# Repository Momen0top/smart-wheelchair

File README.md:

# SmartChair v3 — Complete System

A locally controlled smart robotic wheelchair with Raspberry Pi 3B, 2D LIDAR mapping, A* autonomous navigation, and a Flutter mobile app.

## Project Structure

```
chair/
├── backend/                        # Raspberry Pi (Python/FastAPI)
│   ├── main.py                     # FastAPI + WebSocket server
│   ├── config.py                   # GPIO pins, map grid, safety
│   ├── models.py                   # Pydantic models
│   ├── utils.py                    # Logging
│   ├── motor_controller.py         # 2× L298N DC motor control
│   ├── lidar_scanner.py            # Stepper + VL53L0X 360° scanner
│   ├── mapping_engine.py           # Occupancy grid + Bresenham ray-cast
│   ├── navigator.py                # A* pathfinding + autonomous drive
│   ├── room_manager.py             # rooms.json CRUD
│   ├── command_interpreter.py      # NLP intent extraction
│   ├── pairing.py                  # QR code generation
│   ├── requirements.txt
│   └── test_interpreter.py
│
├── wheelchair_app/                 # Flutter mobile app
│   ├── pubspec.yaml
│   ├── android/.../AndroidManifest.xml
│   └── lib/
│       ├── main.dart               # App shell + bottom nav
│       ├── models/models.dart      # Data classes
│       ├── services/
│       │   ├── api_service.dart    # REST client
│       │   ├── websocket_service.dart # Live map
│       │   └── speech_service.dart # Voice
│       ├── widgets/
│       │   ├── map_painter.dart    # Occupancy grid renderer
│       │   ├── room_dialog.dart    # Room naming
│       │   └── control_pad.dart    # D-pad
│       └── screens/
│           ├── map_screen.dart     # Main map view
│           ├── rooms_screen.dart   # Room list + Go
│           └── pairing_screen.dart # QR/NFC + manual
│
├── esp32_firmware/                 # (v2 ESP32 — optional)
│   └── esp32_controller/
│       └── esp32_controller.ino
│
└── README.md
```

## Architecture

```
┌─────────────────────────────────────────────────────────┐
│                    Raspberry Pi 3B                       │
│                                                         │
│  LIDAR Scanner ──► Mapping Engine ──► Navigator          │
│  (VL53L0X+stepper) (occupancy grid)  (A* pathfinding)  │
│                        │                  │             │
│  Motor Controller ◄────┴──────────────────┘             │
│  (2× L298N GPIO)                                        │
│                                                         │
│  FastAPI Server ──► WebSocket /ws/map                   │
│  Room Manager   ──► rooms.json                          │
│  Command Parser ──► NLP intent extraction               │
│  QR Generator   ──► PNG QR code                         │
└────────────────────┬────────────────────────────────────┘
                     │  Wi-Fi (HTTP + WebSocket)
┌────────────────────▼────────────────────────────────────┐
│                  Flutter App                             │
│  ┌──────────┐  ┌──────────┐  ┌──────────┐              │
│  │ Map View │  │  Rooms   │  │ Connect  │              │
│  │          │  │          │  │          │              │
│  │ Live map │  │ Room list│  │ QR scan  │              │
│  │ Zoom/pan │  │ "Go" nav │  │ NFC tap  │              │
│  │ Tap→room │  │ Delete   │  │ Manual IP│              │
│  │ Voice    │  │          │  │          │              │
│  │ D-pad    │  │          │  │          │              │
│  └──────────┘  └──────────┘  └──────────┘              │
└─────────────────────────────────────────────────────────┘
```

## Setup

### Raspberry Pi
```bash
cd backend/
pip install -r requirements.txt
python main.py        # starts on 0.0.0.0:8000
```

### Flutter App
```bash
cd wheelchair_app/
flutter create .      # generate platform scaffolding
flutter pub get
flutter run           # or: flutter build apk
```

## API Endpoints

| Method | Path | Description |
|--------|------|-------------|
| GET | `/status` | Motor state, scanning, navigating |
| GET | `/map` | Current occupancy grid |
| GET | `/scan` | Latest LIDAR scan |
| GET | `/lidar` | Alias for /scan |
| GET | `/rooms` | List saved rooms |
| POST | `/rooms` | Create/update room |
| DELETE | `/rooms/{name}` | Delete room |
| POST | `/navigate` | Navigate to room |
| POST | `/command` | NLP voice command |
| POST | `/stop` | Emergency stop |
| GET | `/pairing/qr` | QR code PNG |
| GET | `/pairing/info` | Pairing JSON |
| WS | `/ws/map` | Live map stream |

## GPIO Wiring

| Component | BCM Pin | Function |
|-----------|---------|----------|
| Motor A EN | 25 | PWM speed |
| Motor A IN1 | 24 | Direction |
| Motor A IN2 | 23 | Direction |
| Motor B EN | 12 | PWM speed |
| Motor B IN1 | 16 | Direction |
| Motor B IN2 | 20 | Direction |
| Stepper IN1 | 6 | ULN2003 |
| Stepper IN2 | 13 | ULN2003 |
| Stepper IN3 | 19 | ULN2003 |
| Stepper IN4 | 26 | ULN2003 |
| VL53L0X SDA | GPIO 2 | I2C |
| VL53L0X SCL | GPIO 3 | I2C |

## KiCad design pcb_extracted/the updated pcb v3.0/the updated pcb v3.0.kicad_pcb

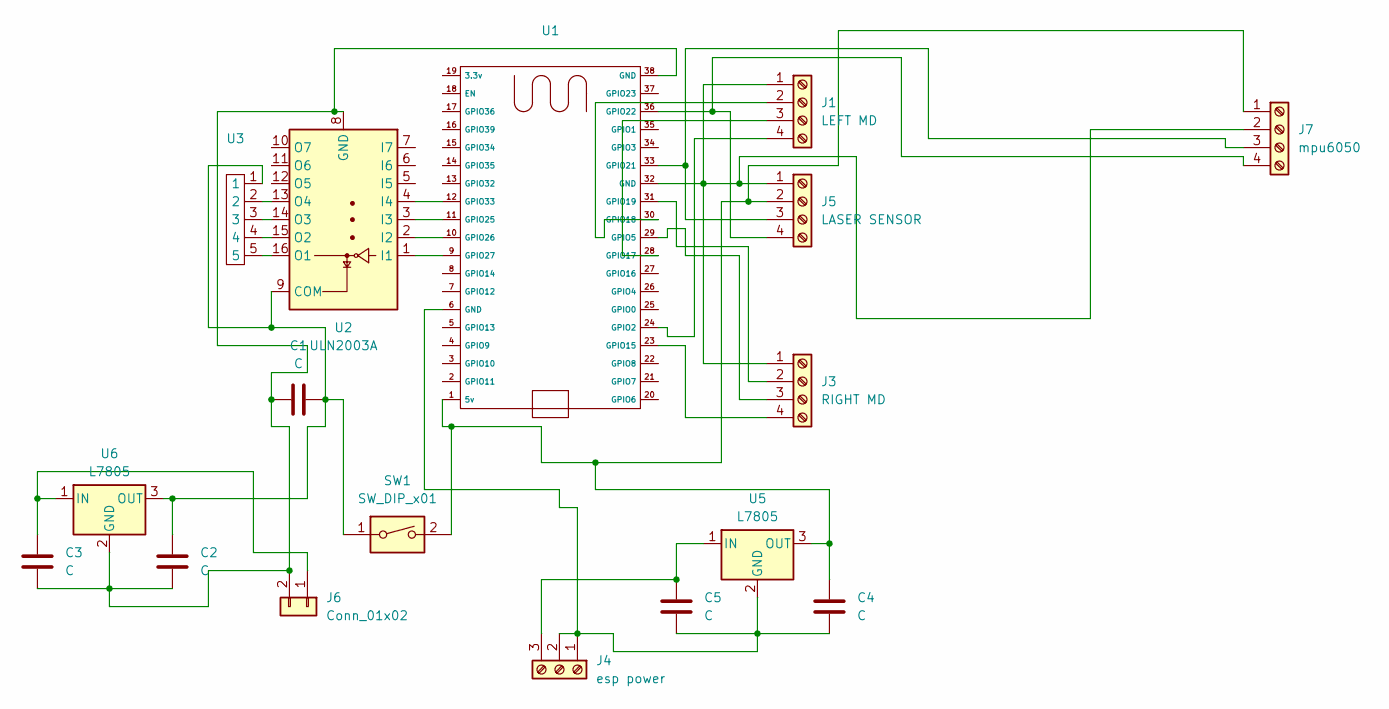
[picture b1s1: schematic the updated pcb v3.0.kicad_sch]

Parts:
C1, C2, C3, C4, C5: C; CP_Radial_D5.0mm_P2.50mm
J1: LEFT MD; JST_XH_B4B-XH-A_1x04_P2.50mm_Vertical
J3: RIGHT MD; JST_XH_B4B-XH-A_1x04_P2.50mm_Vertical
J4: esp power; TerminalBlock_Phoenix_MKDS-1,5-3_1x03_P5.00mm_Horizontal
J5: LASER SENSOR; JST_XH_B4B-XH-A_1x04_P2.50mm_Vertical
J6: Conn_01x02; JST_XH_B2B-XH-A_1x02_P2.50mm_Vertical
J7: mpu6050; PinSocket_1x04_P2.54mm_Vertical
SW1: SW_DIP_x01; SW_DIP_SPSTx01_Slide_9.78x4.72mm_W7.62mm_P2.54mm
U1: ESP32_38pin_fixed
U2: ULN2003A; DIP-16_W7.62mm_LongPads
U3: JST_XH_B5B-XH-A_1x05_P2.50mm_Vertical
U5, U6: L7805; TO-220-3_Vertical

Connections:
unnamed: J1.2, U1.30 (GPIO18)
unnamed: J1.3, U1.28 (GPIO17)
unnamed: J1.4, U1.24 (GPIO2)
unnamed: J1.1 (gnd), J3.1 (gnd), J5.1, J7.2, U1.32 (GND)
unnamed: J3.2, U1.31 (GPIO19)
unnamed: J3.3, U1.29 (GPIO5)
unnamed: J3.4, U1.23 (GPIO15)
unnamed: C4.2, C5.2, J4.1, J4.2, U1.6 (GND), U5.2 (GND)
unnamed: C5.1, J4.3, U5.1 (IN)
unnamed: C4.1, J5.2, J7.1, SW1.2, U1.1 (5v), U5.3 (OUT)
unnamed: J5.3, J7.3, U1.33 (GPIO21)
unnamed: J5.4, J7.4, U1.36 (GPIO22)
unnamed: C3.1, J6.1, U6.1 (IN)
unnamed: C1.2, C2.1, C3.2, J6.2, U1.38 (GND), U2.8 (GND), U6.2 (GND)
unnamed: U1.11 (GPIO25), U2.3 (I3)
unnamed: U1.10 (GPIO26), U2.2 (I2)
unnamed: U1.9 (GPIO27), U2.1 (I1)
unnamed: U1.12 (GPIO33), U2.4 (I4)
unnamed: C1.1, C2.2, SW1.1, U2.9 (COM), U3.1, U6.3 (OUT)
unnamed: U2.16 (O1), U3.5
unnamed: U2.15 (O2), U3.4
unnamed: U2.14 (O3), U3.3
unnamed: U2.13 (O4), U3.2

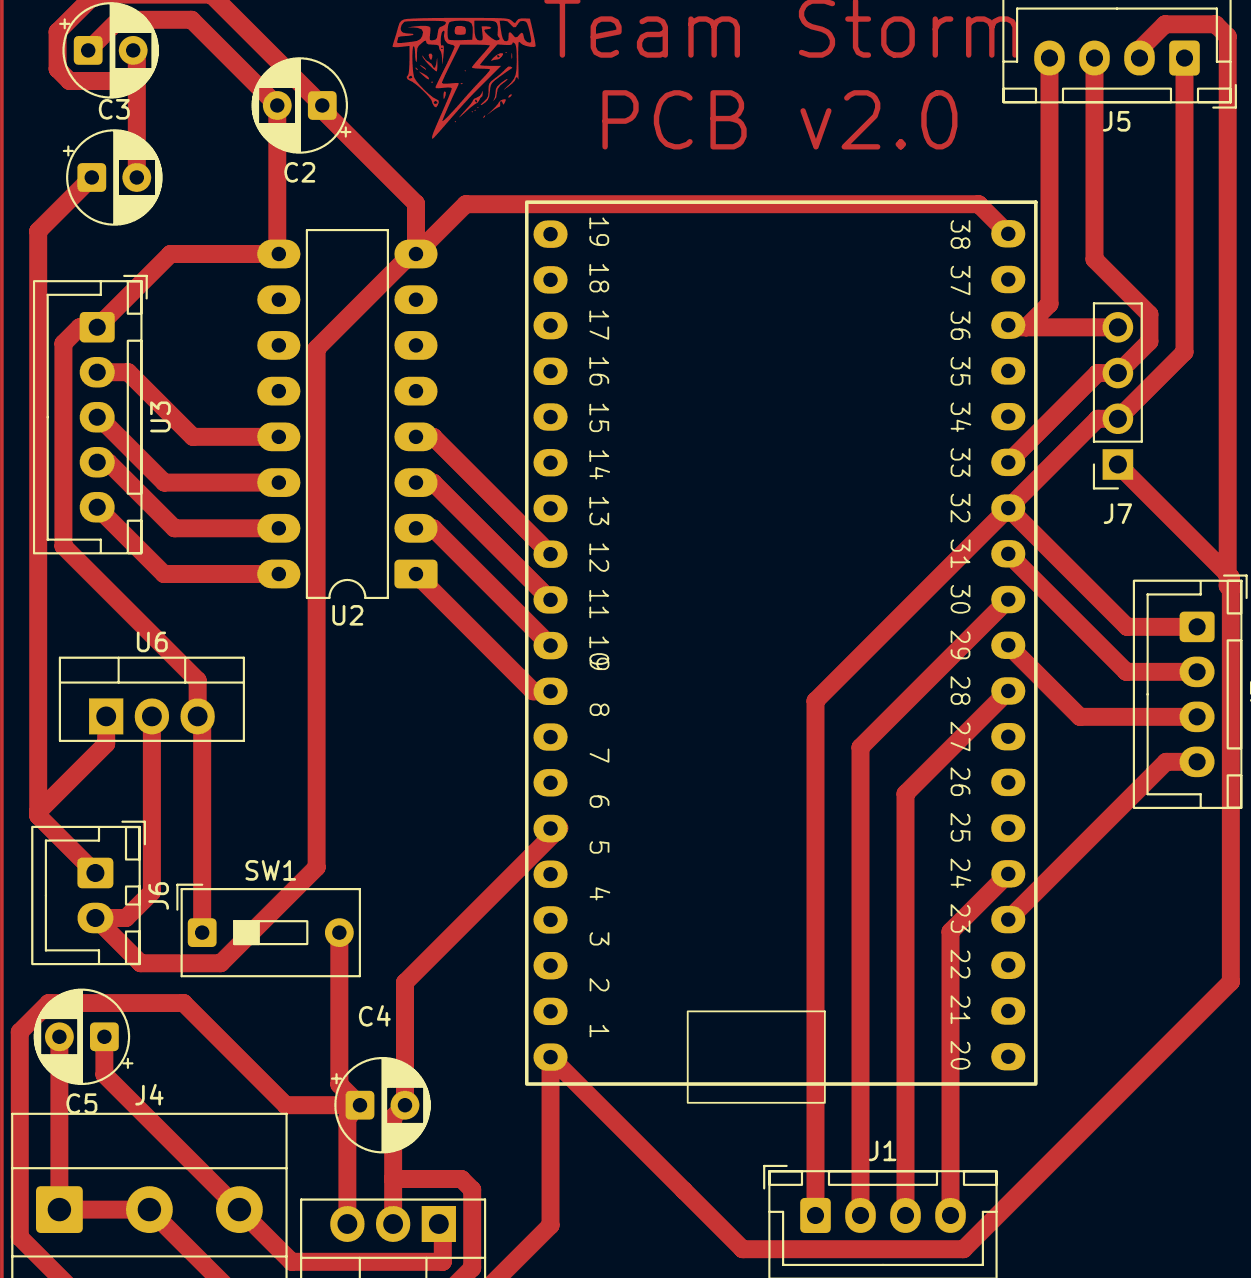
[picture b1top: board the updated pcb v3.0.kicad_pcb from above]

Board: 2 copper layers, 17 parts (0 on the bottom side), 23 nets.

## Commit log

2026-04-29 Update Smart Wheelchair firmware and Pi backend
2026-04-29 Refactor backend to use SerialBridge for ESP32 control and improve robustness
2026-04-29 Complete communication overhaul: Multithreaded ESP32 firmware, WebSocket commands, and optimized Pi backend
2026-04-29 Final production firmware v3.1 and serial port fix
2026-04-29 Final stability fixes: HTTP D-pad, distance key fix, and auto-scan
2026-04-29 Absolute final fail-safe firmware and map rotation fix
